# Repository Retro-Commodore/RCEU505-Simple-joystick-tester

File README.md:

# RCEU505 - Simple Joysticktester
A Simple Joystick Tester as a DIY for Commodore/Atari style digital joystick

Read the document for which resistor values to use for which color LED.  
The LED's can be generic ones from eBay, so resistor values might not be right for your choice.  

Shopping list
* 5x resistors
* 5x 5mm round LEDs
* 1x 9 pin sub-d male
* 1x CR2032 socket
* 1x CR20xx battery (CR2016/CR2025/CR2032 have been tested in the sockets)

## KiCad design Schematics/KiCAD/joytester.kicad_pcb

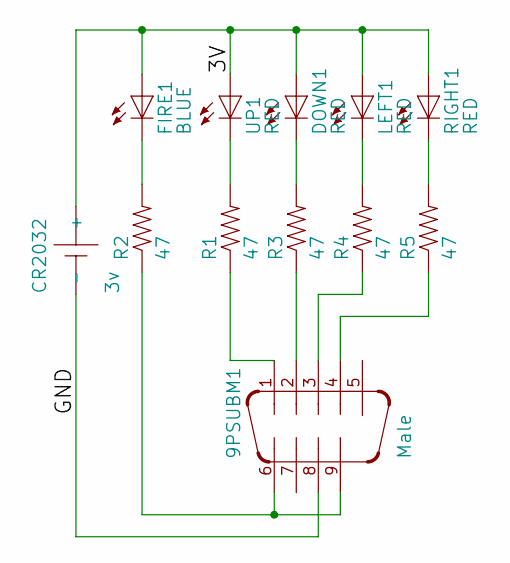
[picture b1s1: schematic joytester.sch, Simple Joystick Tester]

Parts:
9PSUBM1: Male; M09D
CR2032: 3v; SN2032
DOWN1: RED; LED5MM
FIRE1: BLUE; LED5MM
LEFT1: RED; LED5MM
R1, R2, R3, R4, R5: 47; 0207_12
RIGHT1: RED; LED5MM
UP1: RED; LED5MM

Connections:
/3V: CR2032.+, DOWN1.A, FIRE1.A, LEFT1.A, RIGHT1.A, UP1.A
/GND: 9PSUBM1.8, CR2032.-
unnamed: 9PSUBM1.1, R1.1
unnamed: 9PSUBM1.2, R3.1
unnamed: 9PSUBM1.3, R4.1
unnamed: 9PSUBM1.4, R5.1
unnamed: 9PSUBM1.6, 9PSUBM1.9, R2.1
unnamed: DOWN1.K (C), R3.2
unnamed: FIRE1.K (C), R2.2
unnamed: LEFT1.K (C), R4.2
unnamed: R1.2, UP1.K (C)
unnamed: R5.2, RIGHT1.K (C)

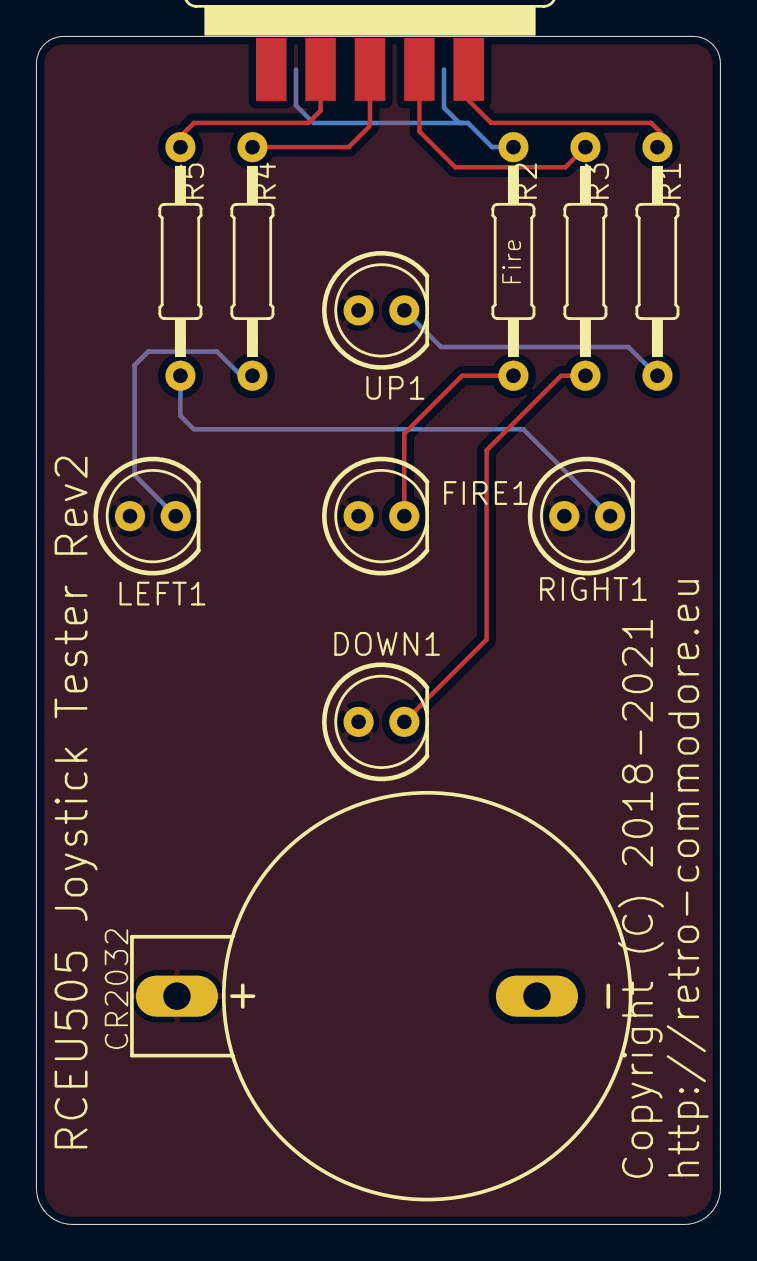
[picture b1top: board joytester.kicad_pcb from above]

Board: 2 copper layers, 38.0 x 66.0 mm, 12 parts (0 on the bottom side), 12 nets.

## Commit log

2018-10-09 Update LICENSE
2020-04-06 cosmetic changes
2020-04-06 Fixing dirnaming
2020-09-27 moved to kicad, while adding support for joystick button nr 2
2020-09-27 Clean up
2021-01-17 Cosmetic changed - added 3d components to 3d view

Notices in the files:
Schematics/Eagle/joytester.sch:
Copyright (c) 2018
Schematics/KiCAD/joytester.kicad_pcb:
Copyright (C) 2018-2021
